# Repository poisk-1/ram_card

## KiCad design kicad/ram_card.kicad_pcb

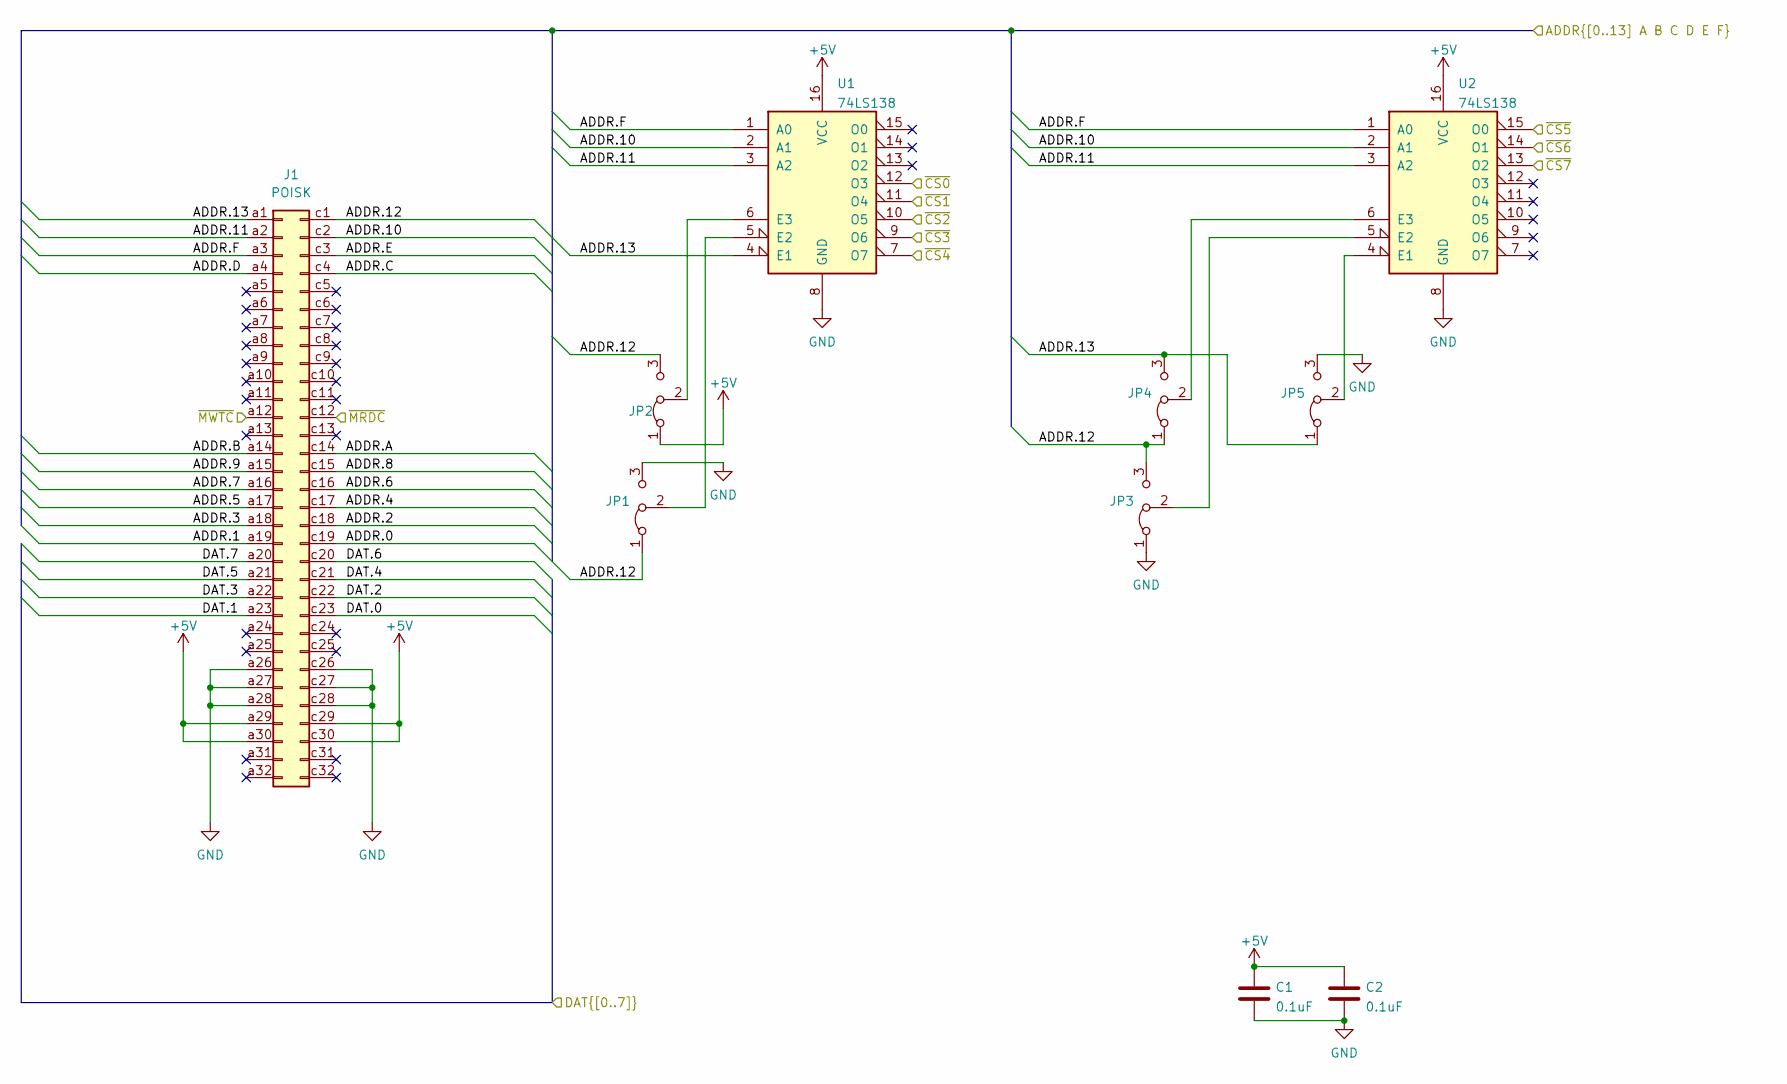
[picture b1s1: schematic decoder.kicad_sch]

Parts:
C1, C2: 0.1uF; C_Disc_D3.0mm_W1.6mm_P2.50mm
J1: POISK; DIN41612_R_2x32_Male_Horizontal_THT
JP1, JP2, JP3, JP4, JP5: Jumper_3_Bridged12; PinHeader_1x03_P2.54mm_Vertical
U1, U2: 74LS138; DIP-16_W7.62mm_Socket

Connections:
+5V: C1.1, C2.1, J1.a29, J1.a30, J1.c29, J1.c30, JP2.1 (A), U1.16 (VCC), U2.16 (VCC); also elsewhere on the board
/banks/ADDR.0: J1.c19; also elsewhere on the board
/banks/ADDR.1: J1.a19; also elsewhere on the board
/banks/ADDR.2: J1.c18; also elsewhere on the board
/banks/ADDR.3: J1.a18; also elsewhere on the board
/banks/ADDR.4: J1.c17; also elsewhere on the board
/banks/ADDR.5: J1.a17; also elsewhere on the board
/banks/ADDR.6: J1.c16; also elsewhere on the board
/banks/ADDR.7: J1.a16; also elsewhere on the board
/banks/ADDR.8: J1.c15; also elsewhere on the board
/banks/ADDR.9: J1.a15; also elsewhere on the board
/banks/ADDR.10: J1.c2, U1.2 (A1), U2.2 (A1)
/banks/ADDR.11: J1.a2, U1.3 (A2), U2.3 (A2)
/banks/ADDR.12: J1.c1, JP1.1 (A), JP2.3 (B), JP3.3 (B), JP4.1 (A)
/banks/ADDR.13: J1.a1, JP4.3 (B), JP5.1 (A), U1.4 (E1)
/banks/ADDR.A: J1.c14; also elsewhere on the board
/banks/ADDR.B: J1.a14; also elsewhere on the board
/banks/ADDR.C: J1.c4; also elsewhere on the board
/banks/ADDR.D: J1.a4; also elsewhere on the board
/banks/ADDR.E: J1.c3; also elsewhere on the board
/banks/ADDR.F: J1.a3, U1.1 (A0), U2.1 (A0)
/banks/DAT.0: J1.c23; also elsewhere on the board
/banks/DAT.1: J1.a23; also elsewhere on the board
/banks/DAT.2: J1.c22; also elsewhere on the board
/banks/DAT.3: J1.a22; also elsewhere on the board
/banks/DAT.4: J1.c21; also elsewhere on the board
/banks/DAT.5: J1.a21; also elsewhere on the board
/banks/DAT.6: J1.c20; also elsewhere on the board
/banks/DAT.7: J1.a20; also elsewhere on the board
/banks/~CS0: U1.12 (O3); also elsewhere on the board
/banks/~CS1: U1.11 (O4); also elsewhere on the board
/banks/~CS2: U1.10 (O5); also elsewhere on the board
/banks/~CS3: U1.9 (O6); also elsewhere on the board
/banks/~CS4: U1.7 (O7); also elsewhere on the board
/banks/~CS5: U2.15 (O0); also elsewhere on the board
/banks/~CS6: U2.14 (O1); also elsewhere on the board
/banks/~CS7: U2.13 (O2); also elsewhere on the board
/banks/~MRDC: J1.c12; also elsewhere on the board
/banks/~MWTC: J1.a12; also elsewhere on the board
GND: C1.2, C2.2, J1.a26, J1.a27, J1.a28, J1.c26, J1.c27, J1.c28, JP1.3 (B), JP3.1 (A), JP5.3 (B), U1.8 (GND), U2.8 (GND); also elsewhere on the board
unnamed: JP1.2 (C), U1.5 (E2)
unnamed: JP2.2 (C), U1.6 (E3)
unnamed: JP3.2 (C), U2.5 (E2)
unnamed: JP4.2 (C), U2.6 (E3)
unnamed: JP5.2 (C), U2.4 (E1)

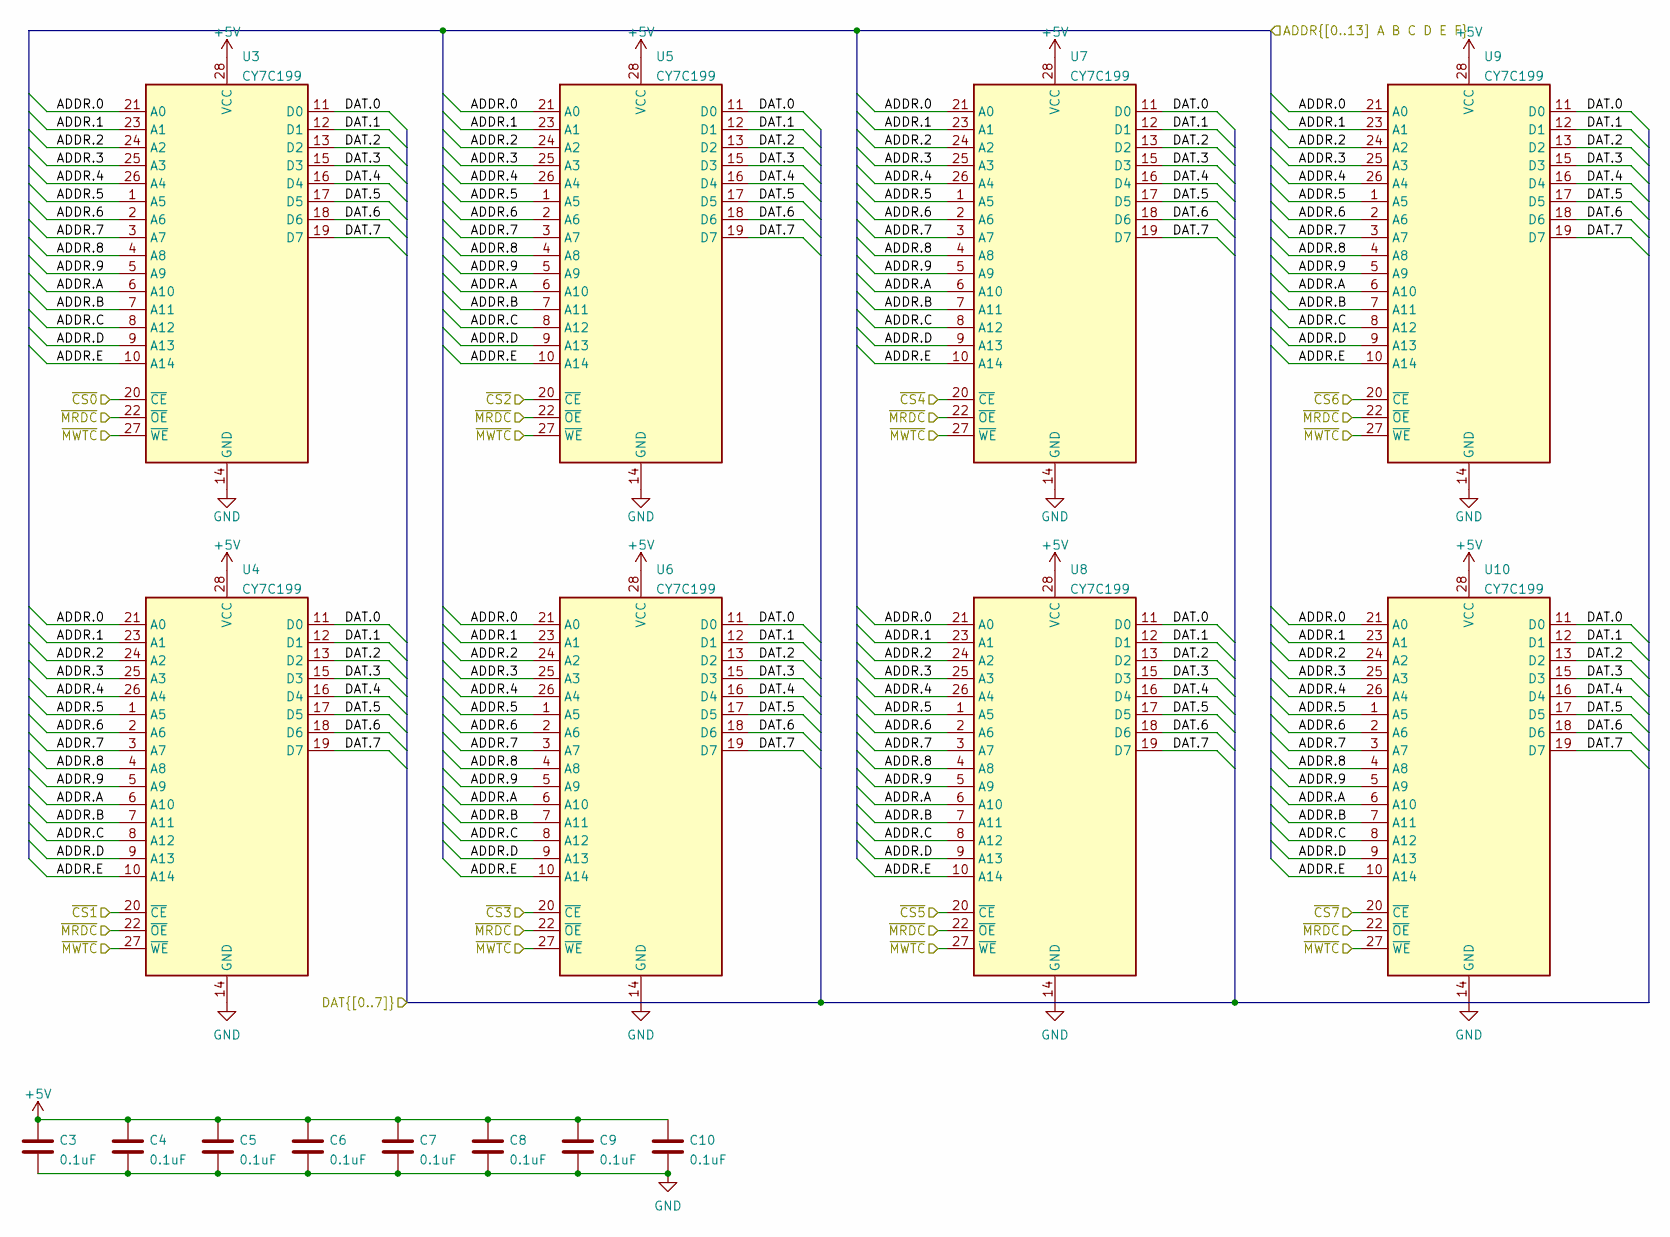
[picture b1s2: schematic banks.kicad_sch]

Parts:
C3, C4, C5, C6, C7, C8, C9, C10: 0.1uF; C_Disc_D3.0mm_W1.6mm_P2.50mm
U3, U4, U5, U6, U7, U8, U9, U10: CY7C199; DIP-28_W7.62mm_Socket

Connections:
+5V: C3.1, C4.1, C5.1, C6.1, C7.1, C8.1, C9.1, C10.1, U3.28 (VCC), U4.28 (VCC), U5.28 (VCC), U6.28 (VCC), U7.28 (VCC), U8.28 (VCC), U9.28 (VCC), U10.28 (VCC); also elsewhere on the board
/banks/ADDR.0: U3.21 (A0), U4.21 (A0), U5.21 (A0), U6.21 (A0), U7.21 (A0), U8.21 (A0), U9.21 (A0), U10.21 (A0); also elsewhere on the board
/banks/ADDR.1: U3.23 (A1), U4.23 (A1), U5.23 (A1), U6.23 (A1), U7.23 (A1), U8.23 (A1), U9.23 (A1), U10.23 (A1); also elsewhere on the board
/banks/ADDR.2: U3.24 (A2), U4.24 (A2), U5.24 (A2), U6.24 (A2), U7.24 (A2), U8.24 (A2), U9.24 (A2), U10.24 (A2); also elsewhere on the board
/banks/ADDR.3: U3.25 (A3), U4.25 (A3), U5.25 (A3), U6.25 (A3), U7.25 (A3), U8.25 (A3), U9.25 (A3), U10.25 (A3); also elsewhere on the board
/banks/ADDR.4: U3.26 (A4), U4.26 (A4), U5.26 (A4), U6.26 (A4), U7.26 (A4), U8.26 (A4), U9.26 (A4), U10.26 (A4); also elsewhere on the board
/banks/ADDR.5: U3.1 (A5), U4.1 (A5), U5.1 (A5), U6.1 (A5), U7.1 (A5), U8.1 (A5), U9.1 (A5), U10.1 (A5); also elsewhere on the board
/banks/ADDR.6: U3.2 (A6), U4.2 (A6), U5.2 (A6), U6.2 (A6), U7.2 (A6), U8.2 (A6), U9.2 (A6), U10.2 (A6); also elsewhere on the board
/banks/ADDR.7: U3.3 (A7), U4.3 (A7), U5.3 (A7), U6.3 (A7), U7.3 (A7), U8.3 (A7), U9.3 (A7), U10.3 (A7); also elsewhere on the board
/banks/ADDR.8: U3.4 (A8), U4.4 (A8), U5.4 (A8), U6.4 (A8), U7.4 (A8), U8.4 (A8), U9.4 (A8), U10.4 (A8); also elsewhere on the board
/banks/ADDR.9: U3.5 (A9), U4.5 (A9), U5.5 (A9), U6.5 (A9), U7.5 (A9), U8.5 (A9), U9.5 (A9), U10.5 (A9); also elsewhere on the board
/banks/ADDR.A: U3.6 (A10), U4.6 (A10), U5.6 (A10), U6.6 (A10), U7.6 (A10), U8.6 (A10), U9.6 (A10), U10.6 (A10); also elsewhere on the board
/banks/ADDR.B: U3.7 (A11), U4.7 (A11), U5.7 (A11), U6.7 (A11), U7.7 (A11), U8.7 (A11), U9.7 (A11), U10.7 (A11); also elsewhere on the board
/banks/ADDR.C: U3.8 (A12), U4.8 (A12), U5.8 (A12), U6.8 (A12), U7.8 (A12), U8.8 (A12), U9.8 (A12), U10.8 (A12); also elsewhere on the board
/banks/ADDR.D: U3.9 (A13), U4.9 (A13), U5.9 (A13), U6.9 (A13), U7.9 (A13), U8.9 (A13), U9.9 (A13), U10.9 (A13); also elsewhere on the board
/banks/ADDR.E: U3.10 (A14), U4.10 (A14), U5.10 (A14), U6.10 (A14), U7.10 (A14), U8.10 (A14), U9.10 (A14), U10.10 (A14); also elsewhere on the board
/banks/DAT.0: U3.11 (D0), U4.11 (D0), U5.11 (D0), U6.11 (D0), U7.11 (D0), U8.11 (D0), U9.11 (D0), U10.11 (D0); also elsewhere on the board
/banks/DAT.1: U3.12 (D1), U4.12 (D1), U5.12 (D1), U6.12 (D1), U7.12 (D1), U8.12 (D1), U9.12 (D1), U10.12 (D1); also elsewhere on the board
/banks/DAT.2: U3.13 (D2), U4.13 (D2), U5.13 (D2), U6.13 (D2), U7.13 (D2), U8.13 (D2), U9.13 (D2), U10.13 (D2); also elsewhere on the board
/banks/DAT.3: U3.15 (D3), U4.15 (D3), U5.15 (D3), U6.15 (D3), U7.15 (D3), U8.15 (D3), U9.15 (D3), U10.15 (D3); also elsewhere on the board
/banks/DAT.4: U3.16 (D4), U4.16 (D4), U5.16 (D4), U6.16 (D4), U7.16 (D4), U8.16 (D4), U9.16 (D4), U10.16 (D4); also elsewhere on the board
/banks/DAT.5: U3.17 (D5), U4.17 (D5), U5.17 (D5), U6.17 (D5), U7.17 (D5), U8.17 (D5), U9.17 (D5), U10.17 (D5); also elsewhere on the board
/banks/DAT.6: U3.18 (D6), U4.18 (D6), U5.18 (D6), U6.18 (D6), U7.18 (D6), U8.18 (D6), U9.18 (D6), U10.18 (D6); also elsewhere on the board
/banks/DAT.7: U3.19 (D7), U4.19 (D7), U5.19 (D7), U6.19 (D7), U7.19 (D7), U8.19 (D7), U9.19 (D7), U10.19 (D7); also elsewhere on the board
/banks/~CS0: U3.20 (~CE); also elsewhere on the board
/banks/~CS1: U4.20 (~CE); also elsewhere on the board
/banks/~CS2: U5.20 (~CE); also elsewhere on the board
/banks/~CS3: U6.20 (~CE); also elsewhere on the board
/banks/~CS4: U7.20 (~CE); also elsewhere on the board
/banks/~CS5: U8.20 (~CE); also elsewhere on the board
/banks/~CS6: U9.20 (~CE); also elsewhere on the board
/banks/~CS7: U10.20 (~CE); also elsewhere on the board
/banks/~MRDC: U3.22 (~OE), U4.22 (~OE), U5.22 (~OE), U6.22 (~OE), U7.22 (~OE), U8.22 (~OE), U9.22 (~OE), U10.22 (~OE); also elsewhere on the board
/banks/~MWTC: U3.27 (~WE), U4.27 (~WE), U5.27 (~WE), U6.27 (~WE), U7.27 (~WE), U8.27 (~WE), U9.27 (~WE), U10.27 (~WE); also elsewhere on the board
GND: C3.2, C4.2, C5.2, C6.2, C7.2, C8.2, C9.2, C10.2, U3.14 (GND), U4.14 (GND), U5.14 (GND), U6.14 (GND), U7.14 (GND), U8.14 (GND), U9.14 (GND), U10.14 (GND); also elsewhere on the board

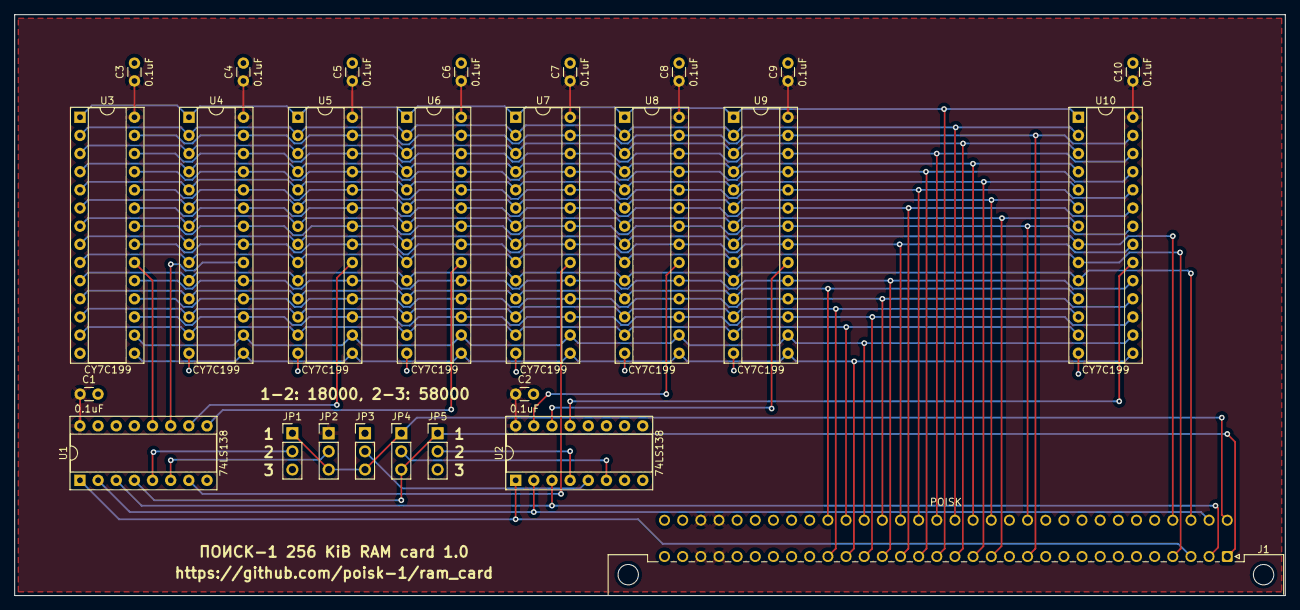
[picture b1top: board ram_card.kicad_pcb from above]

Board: 2 copper layers, 177.8 x 81.3 mm, 26 parts (0 on the bottom side), 45 nets.
